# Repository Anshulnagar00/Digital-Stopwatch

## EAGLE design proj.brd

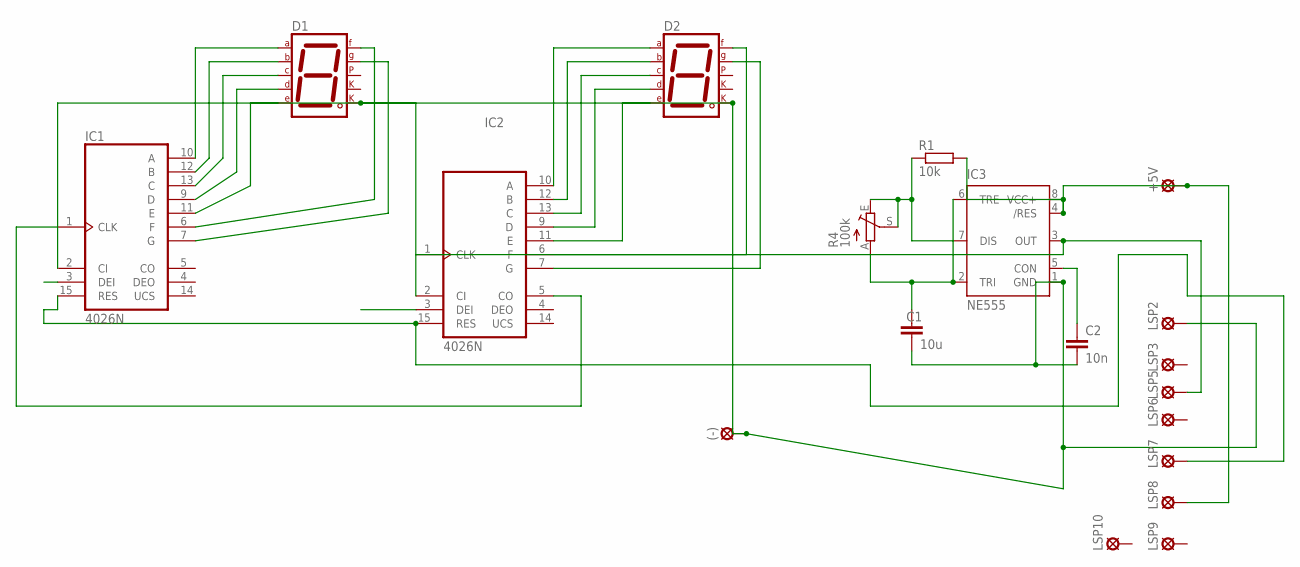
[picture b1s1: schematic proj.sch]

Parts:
(-): SE11
+5V: SE11
C1: 10u; C2.5-2
C2: 10n; C2.5-2
D1, D2: 7SEG-CK; 7SEG-13
IC1, IC2: 4026N; DIL16
IC3: NE555; DIL-08
LSP2, LSP3, LSP5, LSP6, LSP7, LSP8, LSP9, LSP10: SE11
R1: 10k; 0204/7
R4: 100k; RJ9W

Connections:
unnamed: D1.7 (A), IC1.10 (A)
unnamed: D1.6 (B), IC1.12 (B)
unnamed: D1.4 (C), IC1.13 (C)
unnamed: D1.2 (D), IC1.9 (D)
unnamed: D1.1 (E), IC1.11 (E)
unnamed: D1.9 (F), IC1.6 (F)
unnamed: D1.10 (G), IC1.7 (G)
unnamed: D2.7 (A), IC2.10 (A)
unnamed: D2.6 (B), IC2.12 (B)
unnamed: D2.4 (C), IC2.13 (C)
unnamed: D2.2 (D), IC2.9 (D)
unnamed: D2.1 (E), IC2.11 (E)
unnamed: D2.9 (F), IC2.6 (F)
unnamed: D2.10 (G), IC2.7 (G)
unnamed: (-).MP, C1.2, C2.2, D1.8 (CK2), D2.8 (CK2), IC1.2 (CI), IC2.2 (CI), IC3.1 (GND), LSP2.MP
unnamed: IC1.1 (CLK), IC2.5 (CO)
unnamed: +5V.MP, IC3.4 (/RES), IC3.8 (VCC+), LSP8.MP, R1.2
unnamed: IC3.7 (DIS), R1.1, R4.E, R4.S
unnamed: C1.1, IC3.2 (TRI), IC3.6 (TRE), R4.A
unnamed: C2.1, IC3.5 (CON)
unnamed: IC2.1 (CLK), IC3.3 (OUT), LSP5.MP
unnamed: IC1.15 (RES), IC2.15 (RES), LSP7.MP
VDD: IC1.16 (VDD), IC2.3 (DEI), IC2.16 (VDD)
VSS: IC1.8 (VSS), IC2.8 (VSS)

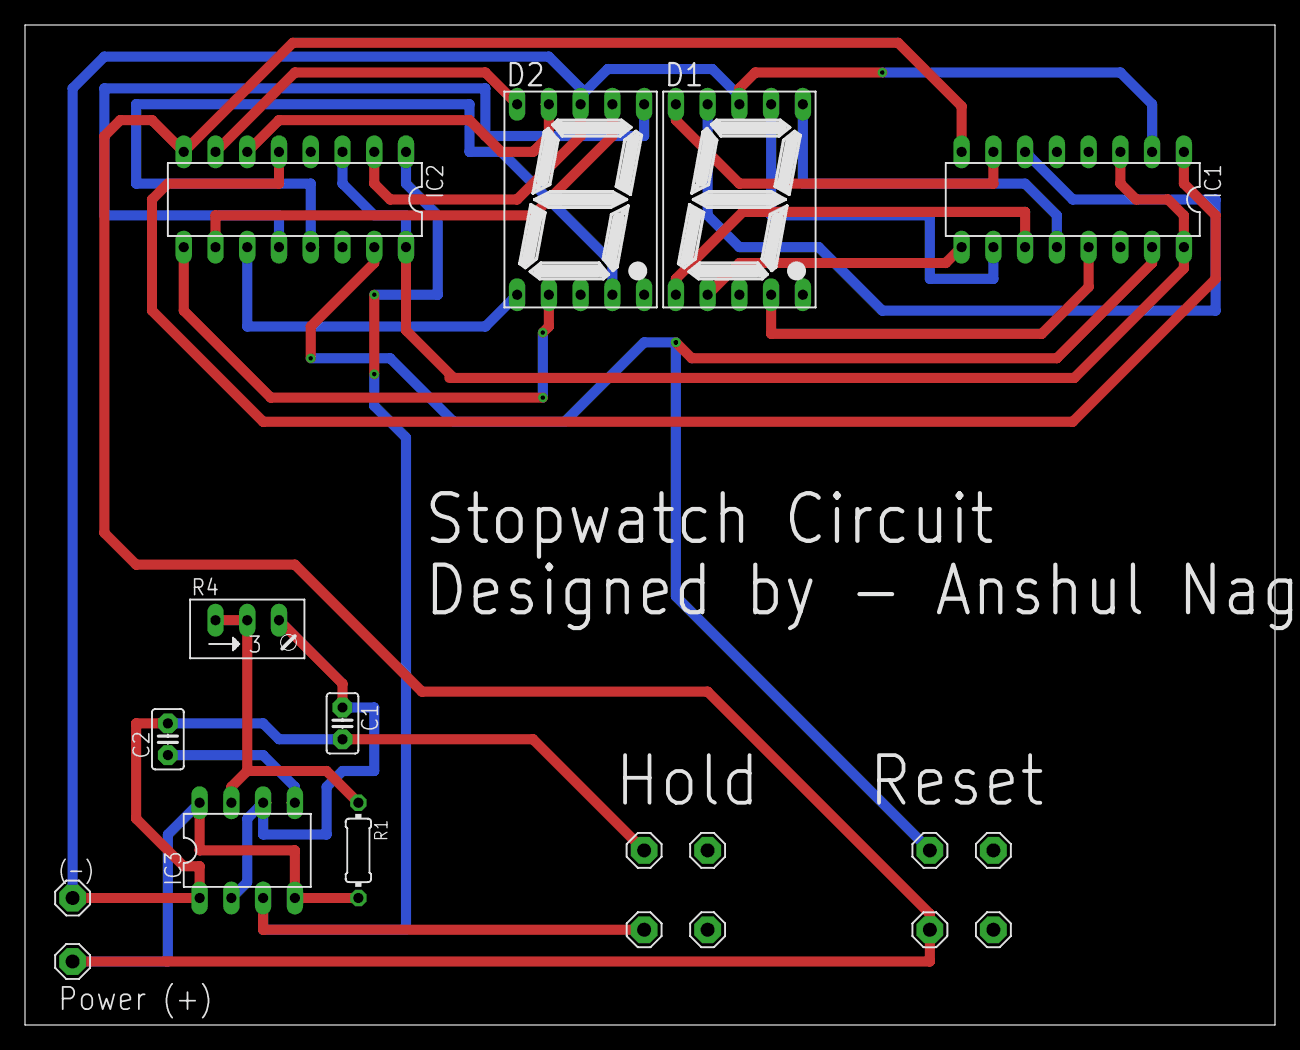
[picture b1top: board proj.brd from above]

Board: 2 copper layers, 100.0 x 80.0 mm, 19 parts (0 on the bottom side), 24 nets.
